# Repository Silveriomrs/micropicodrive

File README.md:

# MicroPicoDrive
 _An internal replacement for the Sinclair QL Microdrive_

---

UPDATE 12/08/2026

> [!NOTE]
> _New revisions of the driver & cartridges with extra EMI & electrical protection and improving signals. Firmware revision 0.14 improved & stable. Firmware & driver tested, tested last cartridge sub-version 'e' for 4 weeks. Added 3D case (STL) created by Jbizze for short cartridge version to its link_.

> [!TIP]
> All material (Gerbers, BOM, etc) & user guides at the bottom of the page.
---

This branch is for the new 1.4 version of the MicroPicoDrive.
This version was created by Silverio MRS (AKA Popopo) from [Dr. Gusman's original version](https://github.com/gusmanb/micropicodrive).

The image above shows the main driver unit and the 2 cartridges versions with long and short wings (_handles_). Long wings allows to manipulate the cartridge easily reducing mechanical pressure. Shorts instead gives an old fashion shape and allows to be stored into the old (used) black boxes of QL time. Also wearing the 3D case created by Jbizze for the short version cartridge.

---
The next link is a fast view with a demo of the device [Short video demo on Youtube](https://youtu.be/dqscsMP1UB8).

---
_Schema of the driver unit that goes inside the QL._

---
_Schema of the cartridge that host the microSD and interact with the user._

# Overview
The project was born to give a solution to the old [ZX Microdrive](https://en.wikipedia.org/wiki/ZX_Microdrive) data systems that relies on tape technology. Due to all those system are more than 50 years old and doesn't exist replacements. This system needed a modern replacement stable, very easy to use, flexible and cheap.

The solution presented relay on Hardware and Software combination. With an OpenSource philosophy that could be easily be continued by thirds parties if needed.

The OpenSource & OpenHardware philosophy also responds to the main idea of allowing everyone to built at any time with inexpensive materials, modify or implements different features.

# Objectives of the project
The project was born with the simple goal to be something that anyone could afford and built, what was exceed by far. Yet, there were some details that make the solution not so universal for everyone (_IMO_). Here is where our story begins.

The point is to exploit all the potential of the concept, increasing the number of features of the device, closer to the Gotek concept but powered up with a lot of amazing and desired features.

The first approach was a full success. Whatever in some design points it was limited:
1. It needs some skills and technical hardware acknowledged the system in advance before to build it.
2. Some users with visual difficulties found it unusable due to the small screen. 
3. If you want to distribute it, you can't without knowing previously where the final user want to place it.

Not only **the hardware have been re-shaped**, but **the code/firmware has been refactored, documented (even more) and modularized** in a way that the skills requirements to modify it, become affordable with lower programming skill than before.

It makes sense if the idea is to get chances of scalability and maintenance by the community or recycle the code/hardware in other similar projects.

## Changes over the original project
**New 1.4 design changes:**

+ Place it in any position (MDV_1 or MDV_2) without physical modification.
+ IDC Cable now go straight to the connector on the QL MB.
+ Removed Status LED from Cartridge due to redundancy information with QL Case LED.
+ Add MicroSD footprint to the Cartridge. From now on, it will be cheaper & elegant to build it up.
+ The board is shorter than original one reducing possible case clashes.
+ RaspBerryPi Pico now is soldered on the bottom of the Driver PCB.
+ The Power regulator has changed the place, allowing to the board be placed in any position (MDV_1 or MDV_2).
+ Solved problem with QL Speaker.
+ Solved problem with QL metal chassis under keyboard.
+ Solved problem with right lateral QL case and the regulator.
+ Sound System ready for sound emulation or new features related with it (Working in progress).
+ Added decoupling capacitors to make signals more stable for oLED & mSD.
+ Added schottky diode on the driver that allows program it without disconecting from the main QL PCB. For extra it gives extra protection.
+ Cartridges now has pads retraived for power lines and detection.

## What is coming (TODO functionalities)

Majority of users find the device functional and accomplish their expectations, however still it keeps some nice surprises to powering it up. **All of then can be activated optionally (_opt_)**.

 **Software/firmware**
- [x] Config file to customize preferences (opt).
- [x] New screen modes with bigger fonts (opt).
- [x] Capability of defining a default image to load when turning on the QL or inserting the cartridge (opt).
- [ ] Direct writing (optional).
- [ ] Direct control from the QL OS over the storage system (mSD).

 **Hardware**
- [ ] Sound emulation of the motor (WiP) (opt).
- [ ] MIDI player (WiP) (opt).
- [ ] Bluetooth cartridge and its APP to load images from other devices (PC, Phone, Tablet...) (opt).

### Some extra add-ons that could come
- [ ] External version of the MDP.
- [ ] Interface I MDP version.

---

# Audio visual material
The next videos were made in order to make easier to everyone the understanding about the integration and use on Sinclair QL systems. 
- [Presentation](https://youtu.be/yyiCoWN6E_A) of the project and its initial goals.
- [How to install it](https://youtu.be/CpoAiAcQRLA) points to keep in mind to not damage your Sinclair QL when installing the MDP into it.
- [User's Guide I](https://youtu.be/wyJjXfhqH4E) user's guide to change the firmware, prepare the SD, customize your preferences & browse it.
- [User's Guide II](https://youtu.be/AZIg0KIsFko) shows how to use the basis functions of the MDTools to create a new MDV image, also it shows the most common mistakes.

# Gerbers, Firmware & more 
To download and make the devices on your own using my design you can access to the Gerbers and Firmwares at the release section:
[Releases Gerbers & Firmware](https://github.com/Silveriomrs/micropicodrive/releases/tag/v1.4)

For detailed information about revisions of drivers or cartridges go to see: [Gerbers Descriptions Section](https://github.com/Silveriomrs/micropicodrive/tree/1.4/Hardware%201.4%20(By%20Popopo)/Gerbers)

For i/BOM check directory: [Schmems & i/BOMs](https://github.com/Silveriomrs/micropicodrive/tree/1.4/Hardware%201.4%20(By%20Popopo)/Schems%20&%20BOMs)

For 3D case created by Jbizze for short cartridge version: [STL from Thingverse](https://www.thingiverse.com/thing:6886864) or to Download directly: [Releases Gerbers & Firmware](https://github.com/Silveriomrs/micropicodrive/releases/tag/v1.4)

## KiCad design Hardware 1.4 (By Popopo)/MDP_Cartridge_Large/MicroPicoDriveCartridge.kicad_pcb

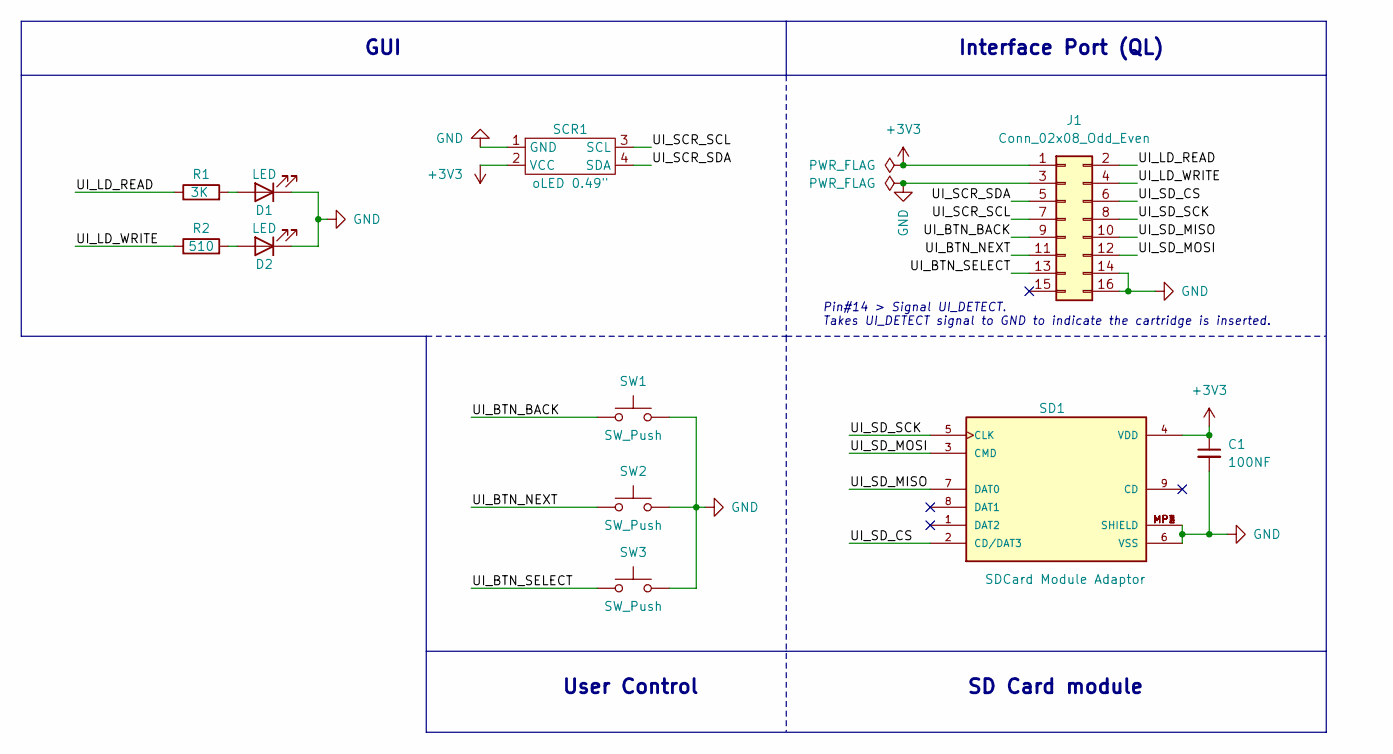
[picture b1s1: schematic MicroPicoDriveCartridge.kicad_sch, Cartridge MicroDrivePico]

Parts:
C1: 100NF; C_0603_1608Metric_Pad1.08x0.95mm_HandSolder
D1, D2: LED; LED_D3.0mm
J1: Conn_02x08_Odd_Even; Edge 2x8pin Male
R1: 3K; R_0603_1608Metric
R2: 510; R_0603_1608Metric
SCR1: oLED 0.49"; Screen
SD1: SDCard Module Adaptor; SDCard_Module_changed
SW1, SW2, SW3: SW_Push; SW_SPST_PTS645Sx43SMTR92

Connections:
+3V3: C1.1, J1.1, SCR1.2 (VCC), SD1.4 (VDD)
/UI_BTN_BACK: J1.9, SW1.1
/UI_BTN_NEXT: J1.11, SW2.1
/UI_BTN_SELECT: J1.13, SW3.1
/UI_LD_READ: J1.2, R1.1
/UI_LD_WRITE: J1.4, R2.1
/UI_SCR_SCL: J1.7, SCR1.3 (SCL)
/UI_SCR_SDA: J1.5, SCR1.4 (SDA)
/UI_SD_CS: J1.6, SD1.2 (CD/DAT3)
/UI_SD_MISO: J1.10, SD1.7 (DAT0)
/UI_SD_MOSI: J1.12, SD1.3 (CMD)
/UI_SD_SCK: J1.8, SD1.5 (CLK)
GND: C1.2, D1.1 (K), D2.1 (K), J1.3, J1.14, J1.16, SCR1.1 (GND), SD1.6 (VSS), SD1.MP1 (SHIELD), SD1.MP2 (SHIELD), SD1.MP3 (SHIELD), SD1.MP4 (SHIELD), SW1.2, SW2.2, SW3.2
unnamed: D1.2 (A), R1.2
unnamed: D2.2 (A), R2.2

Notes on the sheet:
GUI
Pin#14 > Signal UI_DETECT. Takes UI_DETECT signal to GND to indicate the cartridge is inserted.
Interface Port (QL)
User Control
SD Card module

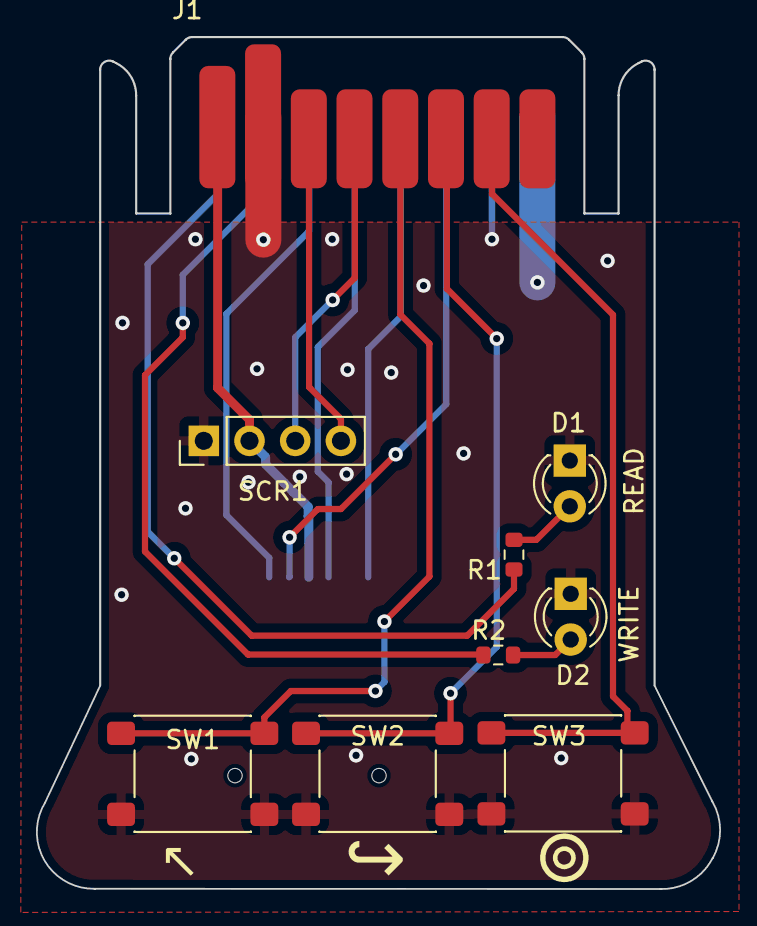
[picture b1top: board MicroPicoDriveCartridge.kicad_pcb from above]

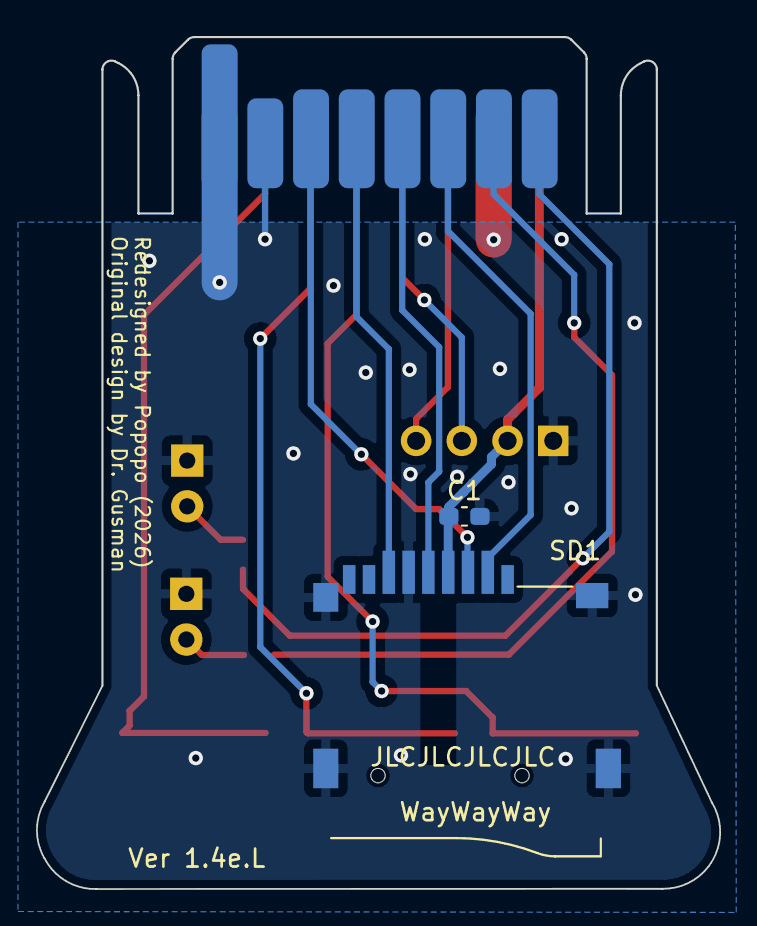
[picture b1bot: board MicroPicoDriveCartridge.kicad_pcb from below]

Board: 2 copper layers, 38.0 x 47.3 mm, 11 parts (2 on the bottom side), 15 nets.

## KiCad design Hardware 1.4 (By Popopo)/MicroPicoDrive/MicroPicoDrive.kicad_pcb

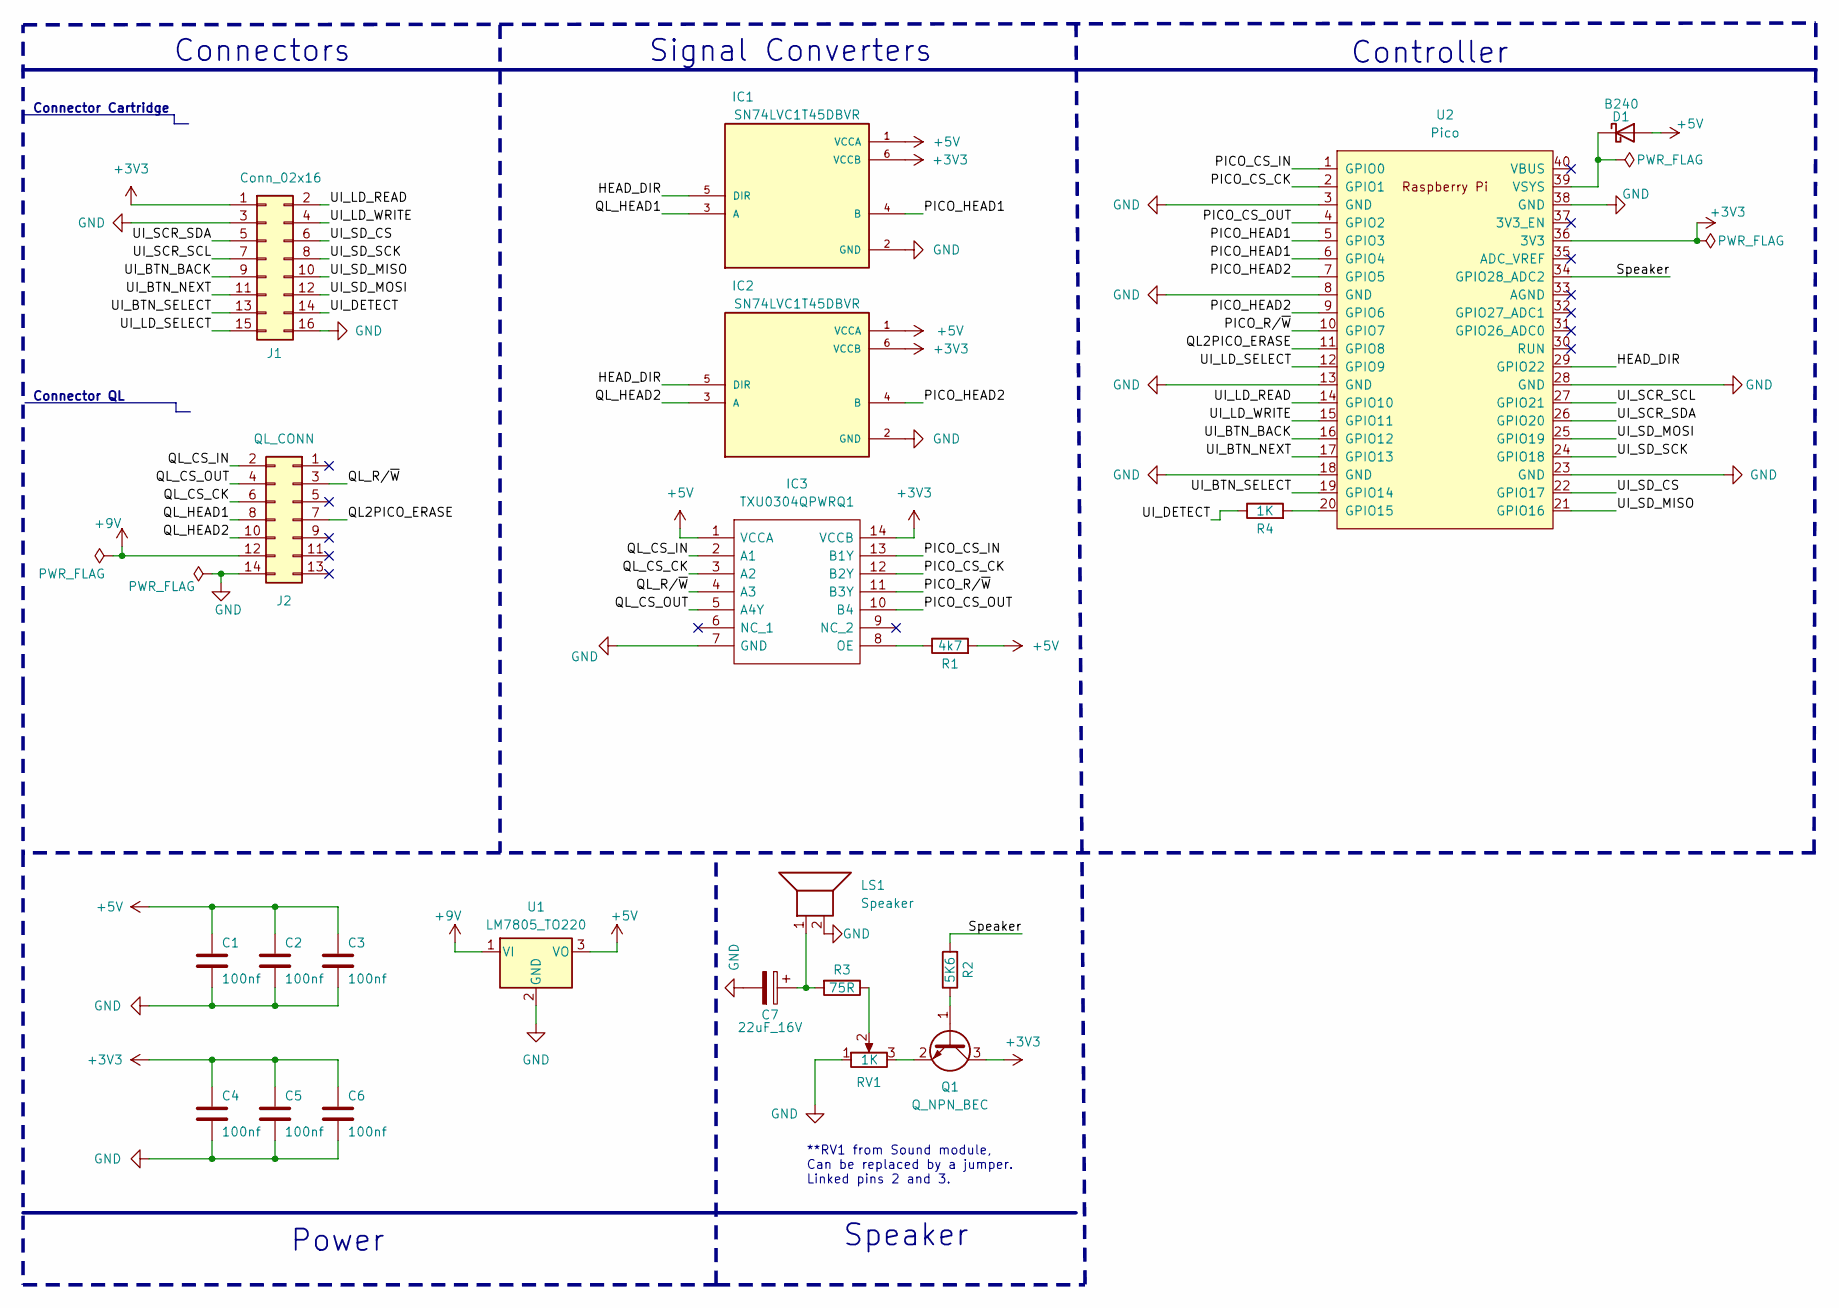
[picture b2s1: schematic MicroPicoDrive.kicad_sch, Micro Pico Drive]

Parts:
C1, C2, C3, C4, C5, C6: 100nf; C_0603_1608Metric
C7: 22uF_16V; CP_Radial_D4.0mm_P1.50mm
D1: B240; D_SMB
IC1, IC2: SN74LVC1T45DBVR; SOT95P280X145-6N; Mouser Part Number 595-SN74LVC1T45DBVR
IC3: TXU0304QPWRQ1; Mouser Part Number 595-TXU0304QPWRQ1
J1: Conn_02x16; Edge_connector_02x08
J2: QL_CONN; CONN_IDC_2x7
LS1: Speaker; PinHeader_1x02_P2.54mm_Vertical
Q1: Q_NPN_BEC; SOT-23W
R1: 4k7; R_0603_1608Metric
R2: 5K6; R_0603_1608Metric
R3: 75R; R_Axial_DIN0207_L6.3mm_D2.5mm_P10.16mm_Horizontal
R4: 1K; R_0603_1608Metric
RV1: 1K; Potentiometer_Bourns_3296W_Vertical
U1: LM7805_TO220; TO-220-3_Vertical
U2: Pico; RPi_Pico_SMD_TH

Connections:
+3V3: C4.1, C5.1, C6.1, IC1.6 (VCCB), IC2.6 (VCCB), IC3.14 (VCCB), J1.1, Q1.3 (C), U2.36 (3V3)
+5V: C1.1, C2.1, C3.1, D1.2 (A), IC1.1 (VCCA), IC2.1 (VCCA), IC3.1 (VCCA), R1.2, U1.3 (VO)
+9V: J2.12, U1.1 (VI)
/HEAD_DIR: IC1.5 (DIR), IC2.5 (DIR), U2.29 (GPIO22)
/PICO_CS_CK: IC3.12 (B2Y), U2.2 (GPIO1)
/PICO_CS_IN: IC3.13 (B1Y), U2.1 (GPIO0)
/PICO_CS_OUT: IC3.10 (B4), U2.4 (GPIO2)
/PICO_HEAD1: IC1.4 (B), U2.5 (GPIO3), U2.6 (GPIO4)
/PICO_HEAD2: IC2.4 (B), U2.7 (GPIO5), U2.9 (GPIO6)
/PICO_R/~W: IC3.11 (B3Y), U2.10 (GPIO7)
/QL2PICO_ERASE: J2.7, U2.11 (GPIO8)
/QL_CS_CK: IC3.3 (A2), J2.6
/QL_CS_IN: IC3.2 (A1), J2.2
/QL_CS_OUT: IC3.5 (A4Y), J2.4
/QL_HEAD1: IC1.3 (A), J2.8
/QL_HEAD2: IC2.3 (A), J2.10
/QL_R/~W: IC3.4 (A3), J2.3
/Speaker: R2.2, U2.34 (GPIO28_ADC2)
/UI_BTN_BACK: J1.9, U2.16 (GPIO12)
/UI_BTN_NEXT: J1.11, U2.17 (GPIO13)
/UI_BTN_SELECT: J1.13, U2.19 (GPIO14)
/UI_DETECT: J1.14, R4.1
/UI_LD_READ: J1.2, U2.14 (GPIO10)
/UI_LD_SELECT: J1.15, U2.12 (GPIO9)
/UI_LD_WRITE: J1.4, U2.15 (GPIO11)
/UI_SCR_SCL: J1.7, U2.27 (GPIO21)
/UI_SCR_SDA: J1.5, U2.26 (GPIO20)
/UI_SD_CS: J1.6, U2.22 (GPIO17)
/UI_SD_MISO: J1.10, U2.21 (GPIO16)
/UI_SD_MOSI: J1.12, U2.25 (GPIO19)
/UI_SD_SCK: J1.8, U2.24 (GPIO18)
GND: C1.2, C2.2, C3.2, C4.2, C5.2, C6.2, C7.2, IC1.2 (GND), IC2.2 (GND), IC3.7 (GND), J1.3, J1.16, J2.14, LS1.2, RV1.1, U1.2 (GND), U2.3 (GND), U2.8 (GND), U2.13 (GND), U2.18 (GND), U2.23 (GND), U2.28 (GND), U2.38 (GND)
unnamed: C7.1, LS1.1, R3.2
unnamed: D1.1 (K), U2.39 (VSYS)
unnamed: IC3.8 (OE), R1.1
unnamed: Q1.1 (B), R2.1
unnamed: Q1.2 (E), RV1.3
unnamed: R3.1, RV1.2
unnamed: R4.2, U2.20 (GPIO15)

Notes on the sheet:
Connector QL
Controller
Power
Connector Cartridge
Speaker
Connectors
Signal Converters
**RV1 from Sound module, Can be replaced by a jumper. Linked pins 2 and 3.

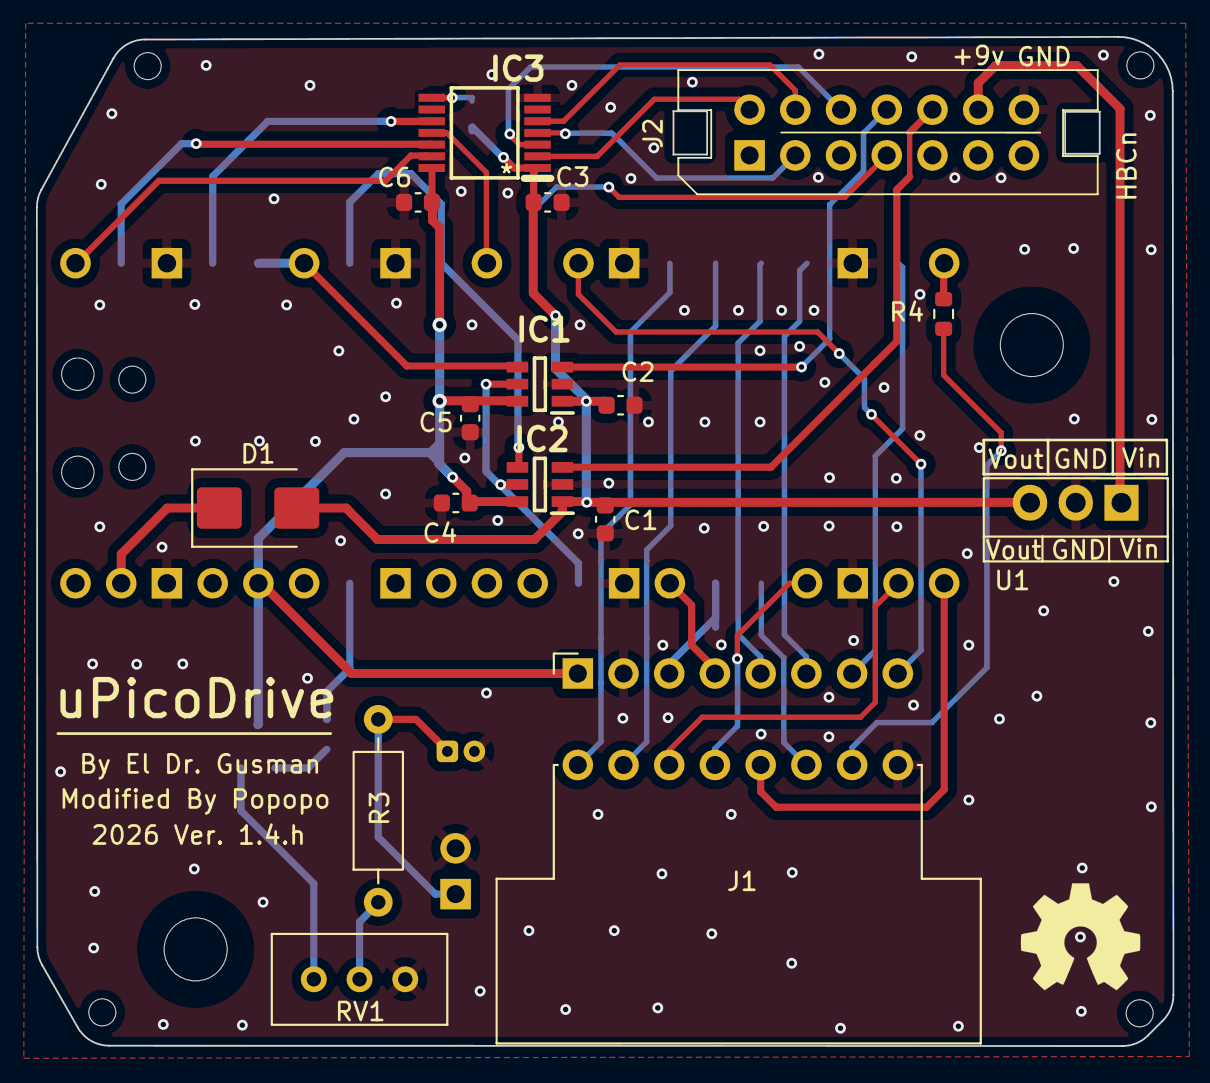
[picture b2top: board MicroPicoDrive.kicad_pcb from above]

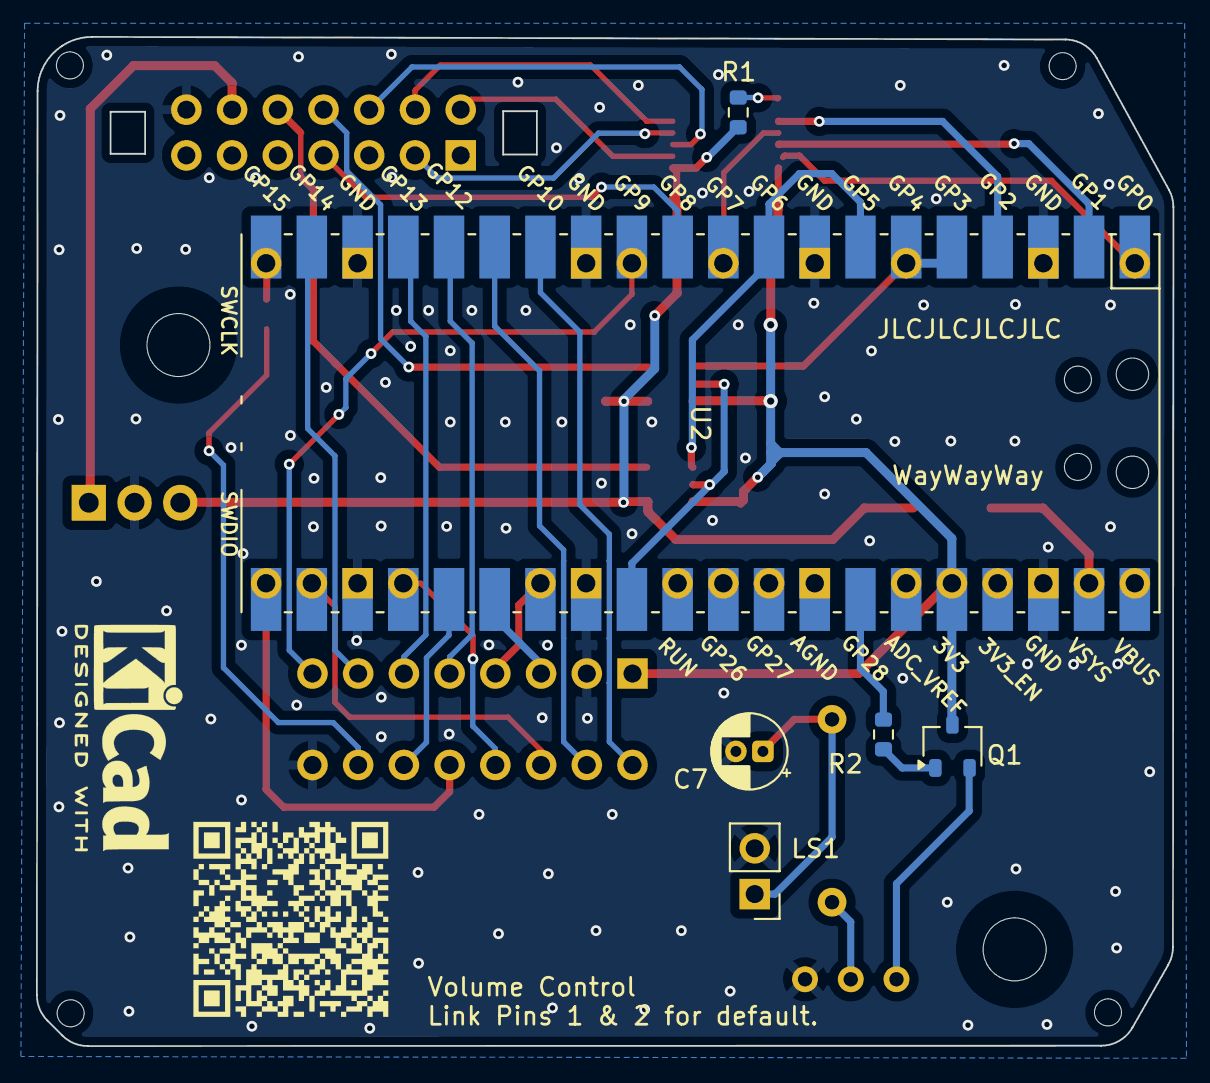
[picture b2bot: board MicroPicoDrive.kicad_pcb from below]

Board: 2 copper layers, 63.1 x 56.1 mm, 30 parts (7 on the bottom side), 39 nets.

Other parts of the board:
Log_KiCad: KiCad-Logo2_5mm_SilkScreen
Log_OpenHardware: OSHW-Symbol_6.7x6mm_SilkScreen
MH1, MH2: MountingHole; MountingHole_3.5mm_safe_screw_area
MH_S1, MH_S2, MH_S3, MH_S4: MountingHole

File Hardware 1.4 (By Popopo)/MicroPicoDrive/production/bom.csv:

Designator,Footprint,Quantity,Value,LCSC Part #
"C1, C2, C3, C4, C5, C6",0603,6,100nf,
C7,CP_Radial_D4.0mm_P1.50mm,1,22uF_16V,
D1,D_SMB,1,B240,
"IC1, IC2",SOT95P280X145-6N,2,SN74LVC1T45DBVR,
IC3,TXU0304QPWRQ1,1,TXU0304QPWRQ1,
J1,Edge_connector_02x08,1,Conn_02x16,
J2,CONN_IDC_2x7,1,QL_CONN,
LS1,PinHeader_1x02_P2.54mm_Vertical,1,Speaker,
"MH1, MH2",MountingHole_3.5mm_safe_screw_area,2,MountingHole,
"MH_S1, MH_S2, MH_S3, MH_S4",,4,MountingHole,
Q1,SOT-23W,1,Q_NPN_BEC,
R1,0603,1,4k7,
R2,0603,1,5K6,
R3,R_Axial_DIN0207_L6.3mm_D2.5mm_P10.16mm_Horizontal,1,75R,
R4,0603,1,1K,
RV1,Potentiometer_Bourns_3296W_Vertical,1,1K,
U1,TO-220-3_Vertical,1,LM7805_TO220,
U2,RPi_Pico_SMD_TH,1,Pico,

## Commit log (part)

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2023-12-24 borrados: MicroPicoDrive/MicroPicoDrive-backups/MicroPicoDrive-2023-12-21_160440.zip modificados: MicroPicoDrive/MicroPicoDrive.kicad_pcb modificados: MicroPicoDrive/MicroPicoDrive.kicad_prl modifica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
2023-12-24 Segundo cambio modificados: README.md borrados: README.md~
2024-06-23 Add files via upload
    My Version of PCBs and Firmware
2024-06-29 WiP screen modes
2024-06-29 WiP re-structure github
2024-07-01 updating info 1
2024-07-01 updating info 3
2024-07-01 updating info 4
2024-07-01 publishing info
2024-07-01 upgrading README
2024-07-07 SCRM2 and bugfixes
2024-07-07 RC8 ignores non valid files and next button change behavior
2024-07-08 little changes
2024-07-08 bugfix DMA and little changes
2024-07-11 SCRM2 and bugfixes 2
2024-07-13 uploading doc
2024-07-14 inner changes
2024-07-15 RC10 almost ready
2024-08-03 RC11 WiP
2024-08-04 RC11 WiP 2
2024-08-04 RC11 WiP 3
2024-08-04 RC11 WiP 4
2024-08-05 RC11 WiP 3 and new MDVs for testing
2024-08-05 Resolving bug 1
2024-08-09 RC11 WiP factoring
2024-08-09 testing doc
2024-08-09 Adding some doc
2024-08-10 updating doc 2
2024-08-10 updating doc 3
2024-08-10 updating doc 4
2024-08-11 updating doc 5
2024-08-11 updating doc 6
2024-08-12 RC11 with bugfix in frozen last FSEntry file
2024-12-01 MDVs demos updated
2024-12-01 MDVs demos updated2
2024-12-07 fixing bug and refactoring
2024-12-12 preRC12
2024-12-12 preRC12 final
2024-12-16 RC13 bugfix when not config file and bugfix in IO function loaddirectly in return value
2025-03-28 RC14: fixed some bugs, working in fixing inherited bugs
2025-03-28 RC14: factorizing
2025-03-31 RC14: day 31, more changes
2025-07-12 new user guide II
2026-05-10 adding diode VSYS
2026-05-12 new rev.f ready
2026-05-29 restructuring and bug fixing
2026-06-09 new diode tested
2026-06-10 Revision driver and firmware, left cartridge rev.e real test
2026-06-13 recovering hard format
2026-06-15 changing DRC and PCB references 1
2026-06-16 changing DRC and PCB references 2
